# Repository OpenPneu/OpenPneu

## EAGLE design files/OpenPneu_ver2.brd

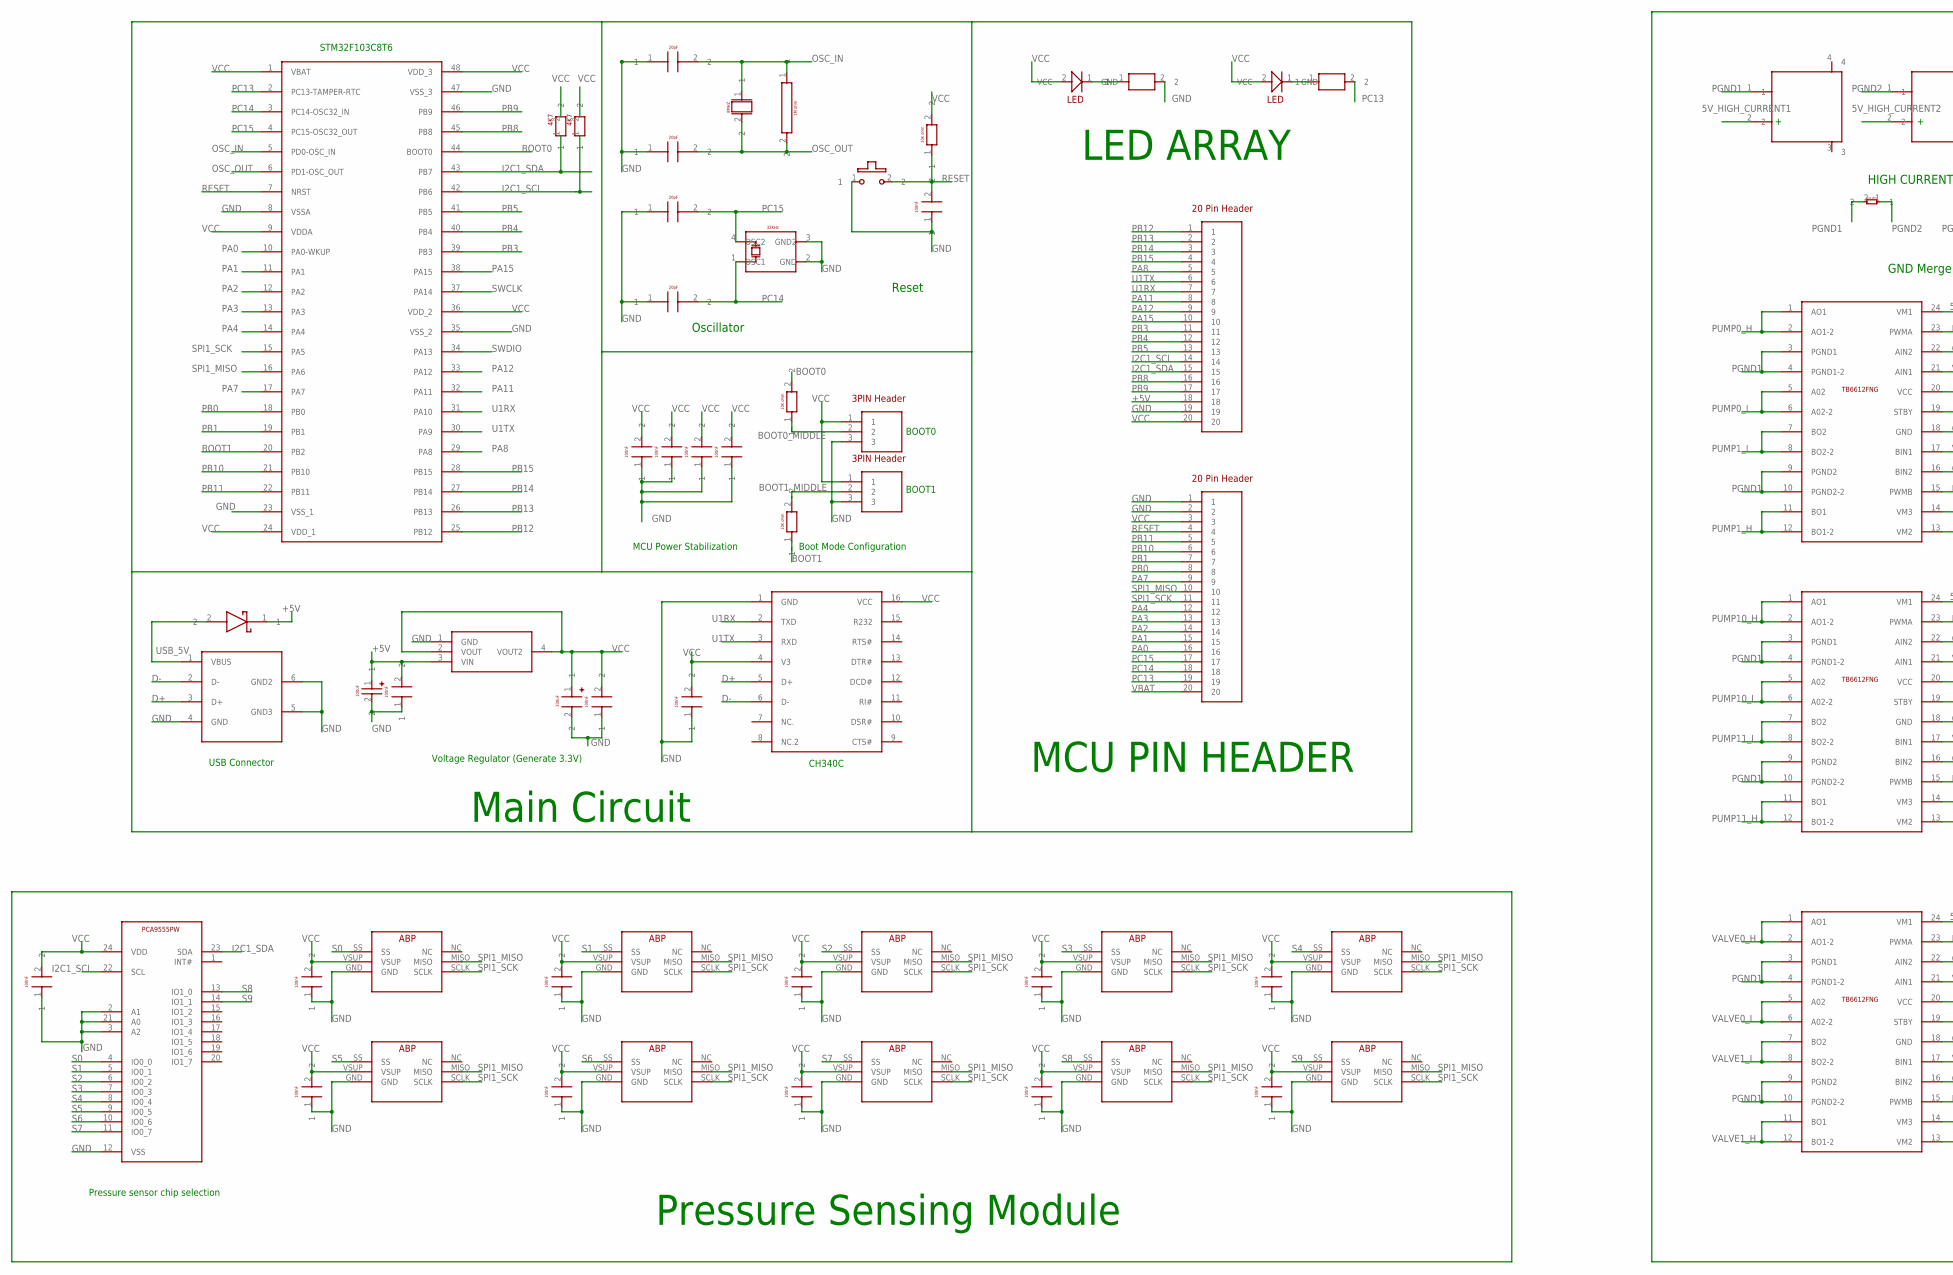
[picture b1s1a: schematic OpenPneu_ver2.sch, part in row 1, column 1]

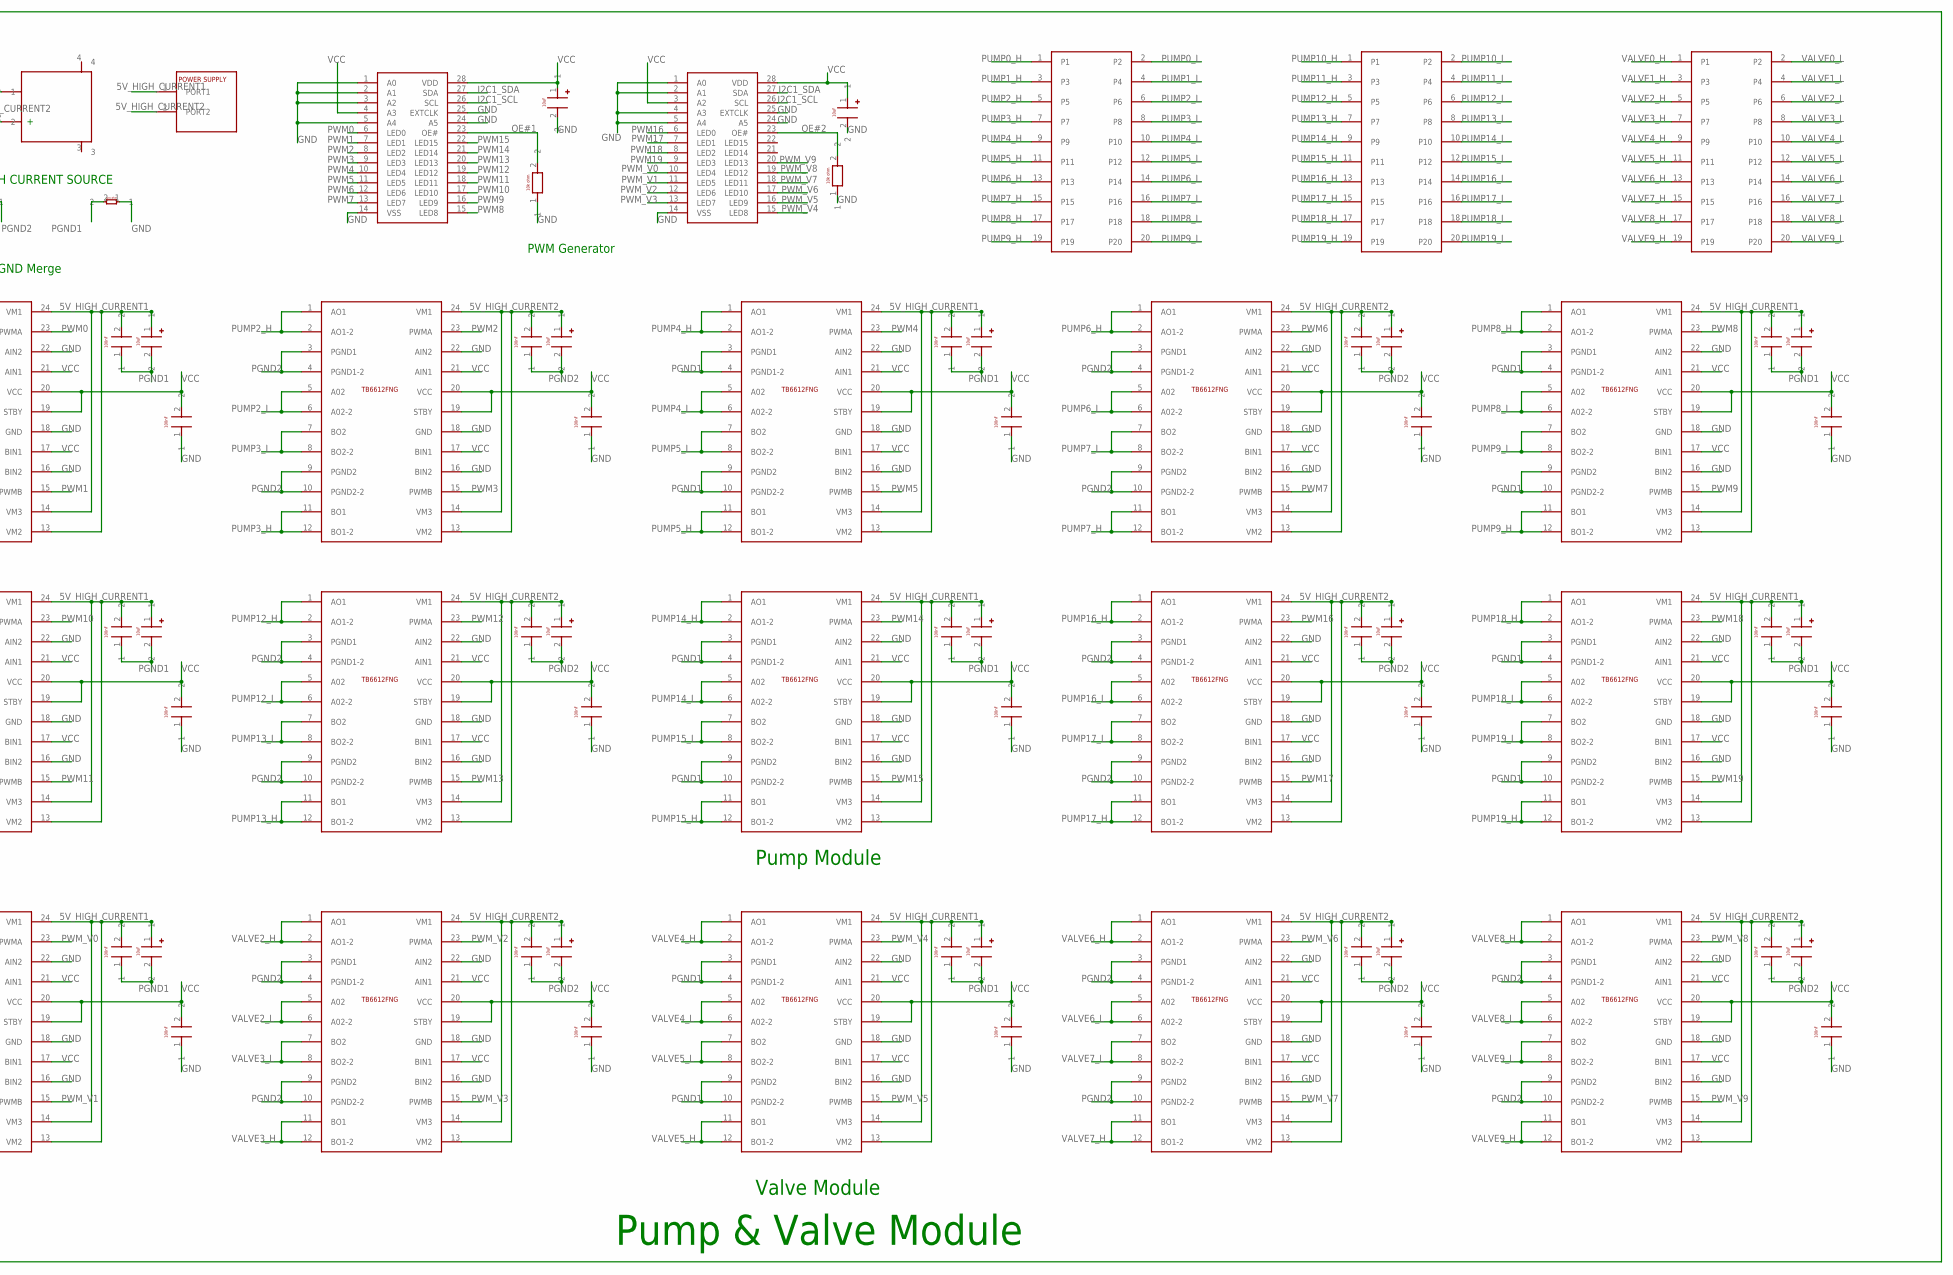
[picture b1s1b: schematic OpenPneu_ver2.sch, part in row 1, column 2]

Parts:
J1, J2: D01-9922046; HDRV20W46P0X254_1X20_5090X254X
U$1: STM32F103_DEVICE; LQFP-48_L7.0-W7.0-P0.50-LS9.27PRIMARY
U$2: 8MHZ_DEVICE; CRYSTAL-SMD_L11.5-W4.8-LS12.A9PRIMARY
U$3, U$4, U$7, U$8: 20PF_DEVICE; C0603_1PRIMARY
U$5: 1M_DEVICE; R0603_1PRIMARY
U$6: 32KHZ_DEVICE; MC-306_4P-L8.0-W3.2-P5.5-BL_1PRIMARY
U$9: VOLTAGE_REGULATOR; SOT-223-3_L6.5-W3.4-P2.30-LS59PRIMARY
U$10: 100UF; CAP-SMD_L6.0-W3.2-R-RD_1PRIMARY
U$11, U$13, U$14, U$15, U$16, U$17, U$21, U$37, U$39, U$40, U$42, U$44, U$46, U$48, U$50, U$52, U$54, U$56, U$58, U$60, U$62, U$64, U$66, U$68, U$70, U$72, U$74, U$76, U$78, U$80, U$82, U$84, U$86, U$88, U$90, U$92, U$94, U$97, U$98, U$100, U$102, U$104, U$106, U$108, U$110, U$112, U$114, U$116, U$130: 100NF_DEVICE; C0603_1PRIMARY
U$12: 330UF_DEVICE; CAP-SMD_L6.0-W3.2-R-RD_1PRIMARY
U$18: USB_NORM_VER2_DEV; USB-B-TH_USB-B01_1PRIMARY
U$19: DIODE_DEVICE; SMA_L4.4-W2.8-LS5.4-RD_1PRIMARY
U$20: CH340C_DEVICE; SOP-16_L10.0-W3.9-P1.27-LS6.C7PRIMARY
U$22, U$23: 3PIN_DEVICE; HDRV20W46P0X254_1X20_5090X254X
U$24, U$25, U$28, U$31, U$34: 10K_DEVICE; R0603_1PRIMARY
U$26: BUTTON_DEVICE; SW-SMD_SMK_JPM1040-XXXXFC_1PRIMARY
U$27: POWER; CONN-TH_P5.00_KF301-5.0-2P_1PRIMARY
U$29, U$30: PCA9685PCA9685; TSSOP-28_L9.7-W4.4-P0.65-LS6FFPRIMARY
U$32, U$33, U$38, U$41, U$45, U$49, U$53, U$57, U$61, U$65, U$69, U$73, U$77, U$81, U$85, U$89, U$93: 10UF_DEVICE; CAP-SMD_L3.5-W2.8-R-RD_1PRIMARY
U$35, U$36, U$43, U$47, U$51, U$55, U$59, U$63, U$67, U$71, U$75, U$79, U$83, U$87, U$91: TB6612FNG; SSOP-24_L8.3-W5.6-P0.65-LS7.93PRIMARY
U$95, U$96, U$99, U$101, U$103, U$105, U$107, U$109, U$111, U$113: ABPDANN1.6BGSA
U$115: TSSOP-24_L7.8-W4.4-P0.65-LS652; TSSOP-24_L7.8-W4.4-P0.65-LS652PRIMARY
U$117, U$118: XT60_DEVICE; CONN-TH_XT60PW-M_1PRIMARY
U$119, U$120: ZERO_OHM; ZERO_OHM_FOOT
U$121, U$122, U$123: PHB-2-10; CONN-TH_PHB-2-10A_1PRIMARY
U$124, U$125: LED; LED0603-RD_1PRIMARY
U$126, U$127: 510_OHM_DEVICE; R0603_1PRIMARY
U$128, U$129: 4K7

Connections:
5V_HIGH_CURRENT1: U$27.1 (PORT1), U$35.13 (VM2), U$35.14 (VM3), U$35.24 (VM1), U$37.2, U$38.1, U$43.13 (VM2), U$43.14 (VM3), U$43.24 (VM1), U$44.2, U$45.1, U$51.13 (VM2), U$51.14 (VM3), U$51.24 (VM1), U$52.2, U$53.1, U$55.13 (VM2), U$55.14 (VM3), U$55.24 (VM1), U$56.2, U$57.1, U$63.13 (VM2), U$63.14 (VM3), U$63.24 (VM1), U$64.2, U$65.1, U$71.13 (VM2), U$71.14 (VM3), U$71.24 (VM1), U$72.2, U$73.1, U$75.13 (VM2), U$75.14 (VM3), U$75.24 (VM1), U$76.2, U$77.1, U$83.13 (VM2), U$83.14 (VM3), U$83.24 (VM1), U$84.2, U$85.1, U$117.2
5V_HIGH_CURRENT2: U$27.2 (PORT2), U$36.13 (VM2), U$36.14 (VM3), U$36.24 (VM1), U$40.2, U$41.1, U$47.13 (VM2), U$47.14 (VM3), U$47.24 (VM1), U$48.2, U$49.1, U$59.13 (VM2), U$59.14 (VM3), U$59.24 (VM1), U$60.2, U$61.1, U$67.13 (VM2), U$67.14 (VM3), U$67.24 (VM1), U$68.2, U$69.1, U$79.13 (VM2), U$79.14 (VM3), U$79.24 (VM1), U$80.2, U$81.1, U$87.13 (VM2), U$87.14 (VM3), U$87.24 (VM1), U$88.2, U$89.1, U$91.13 (VM2), U$91.14 (VM3), U$91.24 (VM1), U$92.2, U$93.1, U$118.2
+5V: J1.18, U$9.3 (VIN), U$10.1, U$11.2, U$19.1
BOOT0: U$1.44 (BOOT0), U$24.2
BOOT0_MIDDLE: U$22.2, U$24.1
BOOT1: U$1.20 (PB2), U$25.1
BOOT1_MIDDLE: U$23.2, U$25.2
D+: U$18.3 (D+), U$20.5 (D+)
D-: U$18.2 (D-), U$20.6 (D-)
GND: J1.19, J2.1, J2.2, U$1.8 (VSSA), U$1.23 (VSS_1), U$1.35 (VSS_2), U$1.47 (VSS_3), U$3.1, U$4.1, U$6.2 (GND), U$6.3 (GND2), U$7.1, U$8.1, U$9.1 (GND), U$10.2, U$11.1, U$12.2, U$13.1, U$14.1, U$15.1, U$16.1, U$17.1, U$18.4 (GND), U$18.5 (GND3), U$18.6 (GND2), U$20.1 (GND), U$21.1, U$22.3, U$23.3, U$26.1, U$29.1 (A0), U$29.2 (A1), U$29.3 (A2), U$29.5 (A4), U$29.14 (VSS), U$29.24 (A5), U$29.25 (EXTCLK), U$30.1 (A0), U$30.2 (A1), U$30.4 (A3), U$30.5 (A4), U$30.14 (VSS), U$30.24 (A5), U$30.25 (EXTCLK), U$31.1, U$32.2, U$33.2, U$34.1, U$35.16 (BIN2), U$35.18 (GND), U$35.22 (AIN2), U$36.16 (BIN2), U$36.18 (GND), U$36.22 (AIN2), U$39.1, U$42.1, U$43.16 (BIN2), U$43.18 (GND), U$43.22 (AIN2), U$46.1, U$47.16 (BIN2), U$47.18 (GND), U$47.22 (AIN2), U$50.1, U$51.16 (BIN2), U$51.18 (GND), U$51.22 (AIN2), U$54.1, U$55.16 (BIN2), U$55.18 (GND), U$55.22 (AIN2), U$58.1, U$59.16 (BIN2), U$59.18 (GND), U$59.22 (AIN2), U$62.1, U$63.16 (BIN2), U$63.18 (GND), U$63.22 (AIN2), U$66.1, U$67.16 (BIN2), U$67.18 (GND), U$67.22 (AIN2), U$70.1, U$71.16 (BIN2), U$71.18 (GND), U$71.22 (AIN2), U$74.1, U$75.16 (BIN2), U$75.18 (GND), U$75.22 (AIN2), U$78.1, U$79.16 (BIN2), U$79.18 (GND), U$79.22 (AIN2), U$82.1, U$83.16 (BIN2), U$83.18 (GND), U$83.22 (AIN2), U$86.1, U$87.16 (BIN2), U$87.18 (GND), U$87.22 (AIN2), U$90.1, U$91.16 (BIN2), U$91.18 (GND), U$91.22 (AIN2), U$94.1, U$95.GND, U$96.GND, U$97.1, U$98.1, U$99.GND, U$100.1, U$101.GND, U$102.1, U$103.GND, U$104.1, U$105.GND, U$106.1, U$107.GND, U$108.1, U$109.GND, U$110.1, U$111.GND, U$112.1, U$113.GND, U$114.1, U$115.2 (A1), U$115.3 (A2), U$115.12 (VSS), U$115.21 (A0), U$116.1, U$120.1, U$126.2, U$130.1
I2C1_SCL: J1.14, U$1.42 (PB6), U$29.26 (SCL), U$30.26 (SCL), U$115.22 (SCL), U$129.1
I2C1_SDA: J1.15, U$1.43 (PB7), U$29.27 (SDA), U$30.27 (SDA), U$115.23 (SDA), U$128.1
unnamed: U$124.1 (GND), U$126.1
unnamed: U$125.1 (GND), U$127.1
OE#1: U$29.23 (OE#), U$31.2
OE#2: U$30.23 (OE#), U$34.2
OSC_IN: U$1.5 (PD0-OSC_IN), U$2.1, U$3.2, U$5.1
OSC_OUT: U$1.6 (PD1-OSC_OUT), U$2.2, U$4.2, U$5.2
PA0: J2.16, U$1.10 (PA0-WKUP)
PA1: J2.15, U$1.11 (PA1)
PA2: J2.14, U$1.12 (PA2)
PA3: J2.13, U$1.13 (PA3)
PA4: J2.12, U$1.14 (PA4)
PA7: J2.9, U$1.17 (PA7)
PA8: J1.5, U$1.29 (PA8)
PA11: J1.8, U$1.32 (PA11)
PA12: J1.9, U$1.33 (PA12)
PA15: J1.10, U$1.38 (PA15)
PB0: J2.8, U$1.18 (PB0)
PB1: J2.7, U$1.19 (PB1)
PB3: J1.11, U$1.39 (PB3)
PB4: J1.12, U$1.40 (PB4)
PB5: J1.13, U$1.41 (PB5)
PB8: J1.16, U$1.45 (PB8)
PB9: J1.17, U$1.46 (PB9)
PB10: J2.6, U$1.21 (PB10)
PB11: J2.5, U$1.22 (PB11)
PB12: J1.1, U$1.25 (PB12)
PB13: J1.2, U$1.26 (PB13)
PB14: J1.3, U$1.27 (PB14)
PB15: J1.4, U$1.28 (PB15)
PC13: J2.19, U$1.2 (PC13-TAMPER-RTC), U$127.2
PC14: J2.18, U$1.3 (PC14-OSC32_IN), U$6.1 (OSC1), U$8.2
PC15: J2.17, U$1.4 (PC15-OSC32_OUT), U$6.4 (OSC2), U$7.2
PGND1: U$35.3 (PGND1), U$35.4 (PGND1-2), U$35.9 (PGND2), U$35.10 (PGND2-2), U$37.1, U$38.2, U$43.3 (PGND1), U$43.4 (PGND1-2), U$43.9 (PGND2), U$43.10 (PGND2-2), U$44.1, U$45.2, U$51.3 (PGND1), U$51.4 (PGND1-2), U$51.9 (PGND2), U$51.10 (PGND2-2), U$52.1, U$53.2, U$55.3 (PGND1), U$55.4 (PGND1-2), U$55.9 (PGND2), U$55.10 (PGND2-2), U$56.1, U$57.2, U$63.3 (PGND1), U$63.4 (PGND1-2), U$63.9 (PGND2), U$63.10 (PGND2-2), U$64.1, U$65.2, U$71.3 (PGND1), U$71.4 (PGND1-2), U$71.9 (PGND2), U$71.10 (PGND2-2), U$72.1, U$73.2, U$75.3 (PGND1), U$75.4 (PGND1-2), U$75.9 (PGND2), U$75.10 (PGND2-2), U$76.1, U$77.2, U$83.3 (PGND1), U$83.4 (PGND1-2), U$83.9 (PGND2), U$83.10 (PGND2-2), U$84.1, U$85.2, U$117.1, U$119.2, U$120.2
PGND2: U$36.3 (PGND1), U$36.4 (PGND1-2), U$36.9 (PGND2), U$36.10 (PGND2-2), U$40.1, U$41.2, U$47.3 (PGND1), U$47.4 (PGND1-2), U$47.9 (PGND2), U$47.10 (PGND2-2), U$48.1, U$49.2, U$59.3 (PGND1), U$59.4 (PGND1-2), U$59.9 (PGND2), U$59.10 (PGND2-2), U$60.1, U$61.2, U$67.3 (PGND1), U$67.4 (PGND1-2), U$67.9 (PGND2), U$67.10 (PGND2-2), U$68.1, U$69.2, U$79.3 (PGND1), U$79.4 (PGND1-2), U$79.9 (PGND2), U$79.10 (PGND2-2), U$80.1, U$81.2, U$87.3 (PGND1), U$87.4 (PGND1-2), U$87.9 (PGND2), U$87.10 (PGND2-2), U$88.1, U$89.2, U$91.3 (PGND1), U$91.4 (PGND1-2), U$91.9 (PGND2), U$91.10 (PGND2-2), U$92.1, U$93.2, U$118.1, U$119.1
PUMP0_H: U$35.1 (AO1), U$35.2 (AO1-2), U$121.1
PUMP0_L: U$35.5 (A02), U$35.6 (A02-2), U$121.2
PUMP1_H: U$35.11 (BO1), U$35.12 (BO1-2), U$121.3
PUMP1_L: U$35.7 (BO2), U$35.8 (BO2-2), U$121.4
PUMP2_H: U$36.1 (AO1), U$36.2 (AO1-2), U$121.5
PUMP2_L: U$36.5 (A02), U$36.6 (A02-2), U$121.6
PUMP3_H: U$36.11 (BO1), U$36.12 (BO1-2), U$121.7
PUMP3_L: U$36.7 (BO2), U$36.8 (BO2-2), U$121.8
PUMP4_H: U$43.1 (AO1), U$43.2 (AO1-2), U$121.9
PUMP4_L: U$43.5 (A02), U$43.6 (A02-2), U$121.10
PUMP5_H: U$43.11 (BO1), U$43.12 (BO1-2), U$121.11
PUMP5_L: U$43.7 (BO2), U$43.8 (BO2-2), U$121.12
PUMP6_H: U$47.1 (AO1), U$47.2 (AO1-2), U$121.13
PUMP6_L: U$47.5 (A02), U$47.6 (A02-2), U$121.14
PUMP7_H: U$47.11 (BO1), U$47.12 (BO1-2), U$121.15
PUMP7_L: U$47.7 (BO2), U$47.8 (BO2-2), U$121.16
PUMP8_H: U$51.1 (AO1), U$51.2 (AO1-2), U$121.17
PUMP8_L: U$51.5 (A02), U$51.6 (A02-2), U$121.18
PUMP9_H: U$51.11 (BO1), U$51.12 (BO1-2), U$121.19
PUMP9_L: U$51.7 (BO2), U$51.8 (BO2-2), U$121.20
PUMP10_H: U$55.1 (AO1), U$55.2 (AO1-2), U$122.1
PUMP10_L: U$55.5 (A02), U$55.6 (A02-2), U$122.2
PUMP11_H: U$55.11 (BO1), U$55.12 (BO1-2), U$122.3
PUMP11_L: U$55.7 (BO2), U$55.8 (BO2-2), U$122.4
PUMP12_H: U$59.1 (AO1), U$59.2 (AO1-2), U$122.5
PUMP12_L: U$59.5 (A02), U$59.6 (A02-2), U$122.6
PUMP13_H: U$59.11 (BO1), U$59.12 (BO1-2), U$122.7
PUMP13_L: U$59.7 (BO2), U$59.8 (BO2-2), U$122.8
PUMP14_H: U$63.1 (AO1), U$63.2 (AO1-2), U$122.9
PUMP14_L: U$63.5 (A02), U$63.6 (A02-2), U$122.10
PUMP15_H: U$63.11 (BO1), U$63.12 (BO1-2), U$122.11
PUMP15_L: U$63.7 (BO2), U$63.8 (BO2-2), U$122.12
PUMP16_H: U$67.1 (AO1), U$67.2 (AO1-2), U$122.13
PUMP16_L: U$67.5 (A02), U$67.6 (A02-2), U$122.14
PUMP17_H: U$67.11 (BO1), U$67.12 (BO1-2), U$122.15
PUMP17_L: U$67.7 (BO2), U$67.8 (BO2-2), U$122.16
PUMP18_H: U$71.1 (AO1), U$71.2 (AO1-2), U$122.17
PUMP18_L: U$71.5 (A02), U$71.6 (A02-2), U$122.18
PUMP19_H: U$71.11 (BO1), U$71.12 (BO1-2), U$122.19
PUMP19_L: U$71.7 (BO2), U$71.8 (BO2-2), U$122.20
PWM0: U$29.6 (LED0), U$35.23 (PWMA)
PWM1: U$29.7 (LED1), U$35.15 (PWMB)
PWM2: U$29.8 (LED2), U$36.23 (PWMA)
PWM3: U$29.9 (LED3), U$36.15 (PWMB)
PWM4: U$29.10 (LED4), U$43.23 (PWMA)
PWM5: U$29.11 (LED5), U$43.15 (PWMB)
PWM6: U$29.12 (LED6), U$47.23 (PWMA)
PWM7: U$29.13 (LED7), U$47.15 (PWMB)
PWM8: U$29.15 (LED8), U$51.23 (PWMA)
PWM9: U$29.16 (LED9), U$51.15 (PWMB)
PWM10: U$29.17 (LED10), U$55.23 (PWMA)
PWM11: U$29.18 (LED11), U$55.15 (PWMB)
PWM12: U$29.19 (LED12), U$59.23 (PWMA)
PWM13: U$29.20 (LED13), U$59.15 (PWMB)
PWM14: U$29.21 (LED14), U$63.23 (PWMA)
PWM15: U$29.22 (LED15), U$63.15 (PWMB)
PWM16: U$30.6 (LED0), U$67.23 (PWMA)
PWM17: U$30.7 (LED1), U$67.15 (PWMB)
PWM18: U$30.8 (LED2), U$71.23 (PWMA)
PWM19: U$30.9 (LED3), U$71.15 (PWMB)
PWM_V0: U$30.10 (LED4), U$75.23 (PWMA)
PWM_V1: U$30.11 (LED5), U$75.15 (PWMB)
PWM_V2: U$30.12 (LED6), U$79.23 (PWMA)
PWM_V3: U$30.13 (LED7), U$79.15 (PWMB)
PWM_V4: U$30.15 (LED8), U$83.23 (PWMA)
PWM_V5: U$30.16 (LED9), U$83.15 (PWMB)
PWM_V6: U$30.17 (LED10), U$87.23 (PWMA)
PWM_V7: U$30.18 (LED11), U$87.15 (PWMB)
PWM_V8: U$30.19 (LED12), U$91.23 (PWMA)
PWM_V9: U$30.20 (LED13), U$91.15 (PWMB)
RESET: J2.4, U$1.7 (NRST), U$26.2, U$28.1, U$130.2
S0: U$95.SS, U$115.4 (IO0_0)
S1: U$96.SS, U$115.5 (IO0_1)
S2: U$99.SS, U$115.6 (IO0_2)
S3: U$101.SS, U$115.7 (IO0_3)
S4: U$103.SS, U$115.8 (IO0_4)
S5: U$105.SS, U$115.9 (IO0_5)
S6: U$107.SS, U$115.10 (IO0_6)
S7: U$109.SS, U$115.11 (IO0_7)
S8: U$111.SS, U$115.13 (IO1_0)
S9: U$113.SS, U$115.14 (IO1_1)
SPI1_MISO: J2.10, U$1.16 (PA6), U$95.MISO, U$96.MISO, U$99.MISO, U$101.MISO, U$103.MISO, U$105.MISO, U$107.MISO, U$109.MISO, U$111.MISO, U$113.MISO
SPI1_SCK: J2.11, U$1.15 (PA5), U$95.SCLK, U$96.SCLK, U$99.SCLK, U$101.SCLK, U$103.SCLK, U$105.SCLK, U$107.SCLK, U$109.SCLK, U$111.SCLK, U$113.SCLK
SWCLK: U$1.37 (PA14)
SWDIO: U$1.34 (PA13)
U1RX: J1.7, U$1.31 (PA10), U$20.2 (TXD)
U1TX: J1.6, U$1.30 (PA9), U$20.3 (RXD)
USB_5V: U$18.1 (VBUS), U$19.2
VALVE0_H: U$75.1 (AO1), U$75.2 (AO1-2), U$123.1
VALVE0_L: U$75.5 (A02), U$75.6 (A02-2), U$123.2
VALVE1_H: U$75.11 (BO1), U$75.12 (BO1-2), U$123.3
VALVE1_L: U$75.7 (BO2), U$75.8 (BO2-2), U$123.4
VALVE2_H: U$79.1 (AO1), U$79.2 (AO1-2), U$123.5
VALVE2_L: U$79.5 (A02), U$79.6 (A02-2), U$123.6
VALVE3_H: U$79.11 (BO1), U$79.12 (BO1-2), U$123.7
VALVE3_L: U$79.7 (BO2), U$79.8 (BO2-2), U$123.8
VALVE4_H: U$83.1 (AO1), U$83.2 (AO1-2), U$123.9
VALVE4_L: U$83.5 (A02), U$83.6 (A02-2), U$123.10
VALVE5_H: U$83.11 (BO1), U$83.12 (BO1-2), U$123.11
VALVE5_L: U$83.7 (BO2), U$83.8 (BO2-2), U$123.12
VALVE6_H: U$87.1 (AO1), U$87.2 (AO1-2), U$123.13
VALVE6_L: U$87.5 (A02), U$87.6 (A02-2), U$123.14
VALVE7_H: U$87.11 (BO1), U$87.12 (BO1-2), U$123.15
VALVE7_L: U$87.7 (BO2), U$87.8 (BO2-2), U$123.16
VALVE8_H: U$91.1 (AO1), U$91.2 (AO1-2), U$123.17
VALVE8_L: U$91.5 (A02), U$91.6 (A02-2), U$123.18
VALVE9_H: U$91.11 (BO1), U$91.12 (BO1-2), U$123.19
VALVE9_L: U$91.7 (BO2), U$91.8 (BO2-2), U$123.20
VBAT: J2.20
VCC: J1.20, J2.3, U$1.1 (VBAT), U$1.9 (VDDA), U$1.24 (VDD_1), U$1.36 (VDD_2), U$1.48 (VDD_3), U$9.2 (VOUT), U$9.4 (VOUT2), U$12.1, U$13.2, U$14.2, U$15.2, U$16.2, U$17.2, U$20.4 (V3), U$20.16 (VCC), U$21.2, U$22.1, U$23.1, U$28.2, U$29.4 (A3), U$29.28 (VDD), U$30.3 (A2), U$30.28 (VDD), U$32.1, U$33.1, U$35.17 (BIN1), U$35.19 (STBY), U$35.20 (VCC), U$35.21 (AIN1), U$36.17 (BIN1), U$36.19 (STBY), U$36.20 (VCC), U$36.21 (AIN1), U$39.2, U$42.2, U$43.17 (BIN1), U$43.19 (STBY), U$43.20 (VCC), U$43.21 (AIN1), U$46.2, U$47.17 (BIN1), U$47.19 (STBY), U$47.20 (VCC), U$47.21 (AIN1), U$50.2, U$51.17 (BIN1), U$51.19 (STBY), U$51.20 (VCC), U$51.21 (AIN1), U$54.2, U$55.17 (BIN1), U$55.19 (STBY), U$55.20 (VCC), U$55.21 (AIN1), U$58.2, U$59.17 (BIN1), U$59.19 (STBY), U$59.20 (VCC), U$59.21 (AIN1), U$62.2, U$63.17 (BIN1), U$63.19 (STBY), U$63.20 (VCC), U$63.21 (AIN1), U$66.2, U$67.17 (BIN1), U$67.19 (STBY), U$67.20 (VCC), U$67.21 (AIN1), U$70.2, U$71.17 (BIN1), U$71.19 (STBY), U$71.20 (VCC), U$71.21 (AIN1), U$74.2, U$75.17 (BIN1), U$75.19 (STBY), U$75.20 (VCC), U$75.21 (AIN1), U$78.2, U$79.17 (BIN1), U$79.19 (STBY), U$79.20 (VCC), U$79.21 (AIN1), U$82.2, U$83.17 (BIN1), U$83.19 (STBY), U$83.20 (VCC), U$83.21 (AIN1), U$86.2, U$87.17 (BIN1), U$87.19 (STBY), U$87.20 (VCC), U$87.21 (AIN1), U$90.2, U$91.17 (BIN1), U$91.19 (STBY), U$91.20 (VCC), U$91.21 (AIN1), U$94.2, U$95.VSUP, U$96.VSUP, U$97.2, U$98.2, U$99.VSUP, U$100.2, U$101.VSUP, U$102.2, U$103.VSUP, U$104.2, U$105.VSUP, U$106.2, U$107.VSUP, U$108.2, U$109.VSUP, U$110.2, U$111.VSUP, U$112.2, U$113.VSUP, U$114.2, U$115.24 (VDD), U$116.2, U$124.2 (VCC), U$125.2 (VCC), U$128.2, U$129.2

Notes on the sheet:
STM32F103C8T6
Oscillator
Voltage Regulator (Generate 3.3V)
USB Connector
CH340C
BOOT0
BOOT1
Boot Mode Configuration
MCU Power Stabilization
Reset
Main Circuit
Pump Module
PWM Generator
Pump & Valve Module
Valve Module
Pressure Sensing Module
Pressure sensor chip selection
GND Merge
HIGH CURRENT SOURCE
MCU PIN HEADER
LED ARRAY

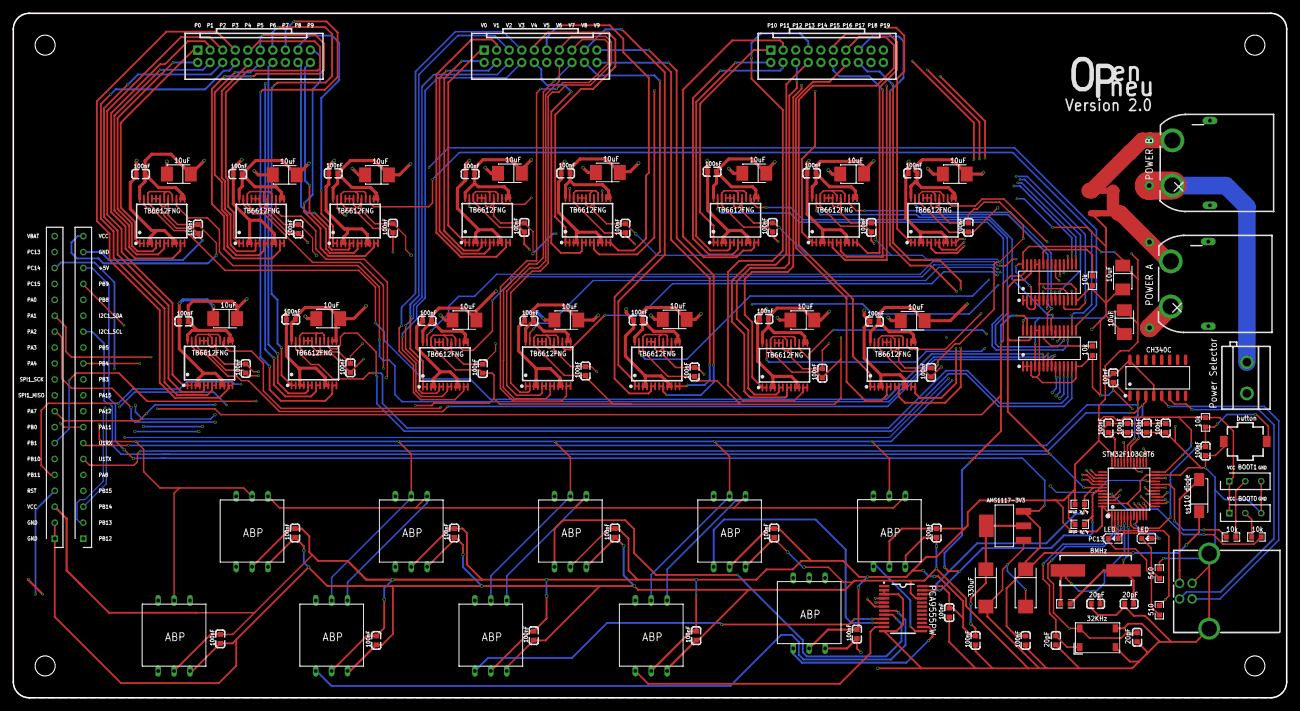
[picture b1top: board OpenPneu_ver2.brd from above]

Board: 4 copper layers, 203.2 x 109.2 mm, 132 parts (0 on the bottom side), 153 nets.

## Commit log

2022-09-15 COMMENT TO DESCRIBE THE INTENTION OF THE COMMIT
